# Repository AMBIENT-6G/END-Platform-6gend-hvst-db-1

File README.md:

# 6gend-hvst-db-1

Dual-Source Energy Harvesting Daughter Board for the END Platform

Part of the **AMBIENT-6G Energy Neutral Device (END) Platform**:
https://github.com/AMBIENT-6G/END-Platform

## Overview

The **6gend-hvst-db-1** is a dual-source energy harvesting daughter board for the END Platform based on the **e-peas AEM13921** energy harvesting PMIC. The board is intended as a research platform for investigating hybrid energy harvesting systems that combine **RF energy harvesting** with a second ambient energy source such as photovoltaic, thermal, vibration, or other DC energy harvesters.

The AEM13921 integrates two independent harvesting inputs, each featuring configurable Maximum Power Point Tracking (MPPT) or constant-voltage regulation. Harvested energy is stored in an external rechargeable storage element and supplied to the application through an integrated high-efficiency buck converter.

The board interfaces with an END Platform main board through the standard 12-pin END Platform connector and provides monitoring and configuration capabilities through an I²C interface.

## Features

- e-peas **AEM13921** dual-source energy harvesting PMIC
- Two independent energy harvesting inputs
- Simultaneous harvesting from both sources
- MPPT operation on both harvesting inputs
- Constant-voltage harvesting mode support
- Dedicated **5 V charging input**
- Integrated storage management
- Support for:
  - Supercapacitors
  - Lithium-Ion Capacitors (LiC)
  - Li-Ion batteries
  - LiPo batteries
- Integrated overcharge protection
- Integrated overdischarge protection
- Temperature monitoring of the storage element
- Configurable safety thresholds
- Average Power Monitoring (APM) through I²C
- Integrated high-efficiency buck converter
- Dynamic configuration through I²C
- Hardware configuration through solder-selectable GPIO settings
- Cold start from as low as **275 mV / 1.5 µW**
- Harvesting operation down to **120 mV after startup**
- END Platform compatible connector interface

## Board Image

[Picture of the PCB design in KiCAD](6gend-hvst-db-1.png)

## Purpose

The primary purpose of this board is to support research into:

- Hybrid energy harvesting systems
- RF energy harvesting
- Multi-source energy management
- Energy-neutral IoT systems
- Ambient energy harvesting optimization
- Storage technology evaluation
- Power-aware embedded systems
- Ultra-low-power wireless sensor nodes
- Energy availability monitoring and prediction

Typical applications combine an RF harvesting source with a second energy source such as:

- Solar cells
- Thermoelectric generators (TEGs)
- Piezoelectric harvesters
- Vibration harvesters
- Pulsed energy sources
- Other low-power DC sources

## Hardware Architecture

### AEM13921 Energy Harvesting PMIC

The board is built around the **e-peas AEM13921**, an ultra-efficient dual-source energy harvesting power management IC.

Key capabilities include:

- Two independent boost converters
- Independent MPPT configuration for each source
- Constant-voltage source regulation
- Simultaneous harvesting from both inputs
- Integrated storage charging and protection
- Integrated buck converter output
- Energy flow monitoring through Average Power Monitoring (APM)

The device can determine how much energy has been transferred from each harvesting source and from the 5 V charger into the storage element, as well as the energy delivered from storage to the load through its APM functionality.

### Energy Harvesting Inputs

The AEM13921 supports two harvesting channels.

Each input can be independently configured for:

- Open-circuit voltage ratio MPPT
- Constant-voltage regulation

This makes it possible to optimize energy extraction from a broad range of harvesting technologies while simultaneously harvesting from both sources.

A common use case is:

- Source 1: RF energy harvester
- Source 2: Solar cell

but other combinations are equally possible.

### 5 V Charging Input

In addition to the harvesting inputs, the board provides a dedicated **5 V charging input**.

This interface allows:

- Rapid charging of the storage element
- Recovery from depleted storage conditions
- Laboratory testing and characterization
- Development without requiring ambient energy sources

### Storage Management

The board supports a wide variety of rechargeable storage technologies including:

- Supercapacitors
- Lithium-Ion Capacitors (LiC)
- Lithium-Ion batteries
- Lithium-Polymer batteries

The AEM13921 provides configurable:

- Charge-ready thresholds
- Overcharge protection
- Overdischarge protection

These protection mechanisms increase storage lifetime and ensure safe operation.

### Thermal Monitoring

A dedicated temperature monitoring circuit is provided for the storage element.

This functionality allows:

- Monitoring storage temperature through the PMIC
- Over-temperature protection
- Under-temperature protection
- Safe charging and discharging operation

Temperature protection can be configured independently for charge and discharge conditions.

### Buck Converter Output

The harvested and stored energy is delivered to the application through the integrated high-efficiency buck converter.

Features include:

- Output voltage configurable between 0.6 V and 3.3 V
- High conversion efficiency
- Output current capability up to 100 mA

This allows efficient powering of ultra-low-power sensors, microcontrollers, and wireless communication systems.

### Configuration Interface

The board supports two configuration methods:

#### GPIO Configuration

The AEM13921 configuration pins can be statically configured using solder bridges on the PCB.

Depending on the solder bridge population, configuration pins may be tied:

- High
- Low

This allows standalone operation without software configuration.

#### I²C Configuration

All important system parameters can also be configured dynamically through I²C.

Available functionality includes:

- Reading system status
- Monitoring energy flow information
- Modifying PMIC operating parameters
- Reconfiguring protection thresholds
- Harvesting optimization

## Connector Pinout

The board follows the END Platform harvesting connector definition.

| Pin | Function |
|------|----------|
| 1 | NC |
| 2 | IRQ |
| 3 | SCL |
| 4 | SDA |
| 5 | GND |
| 6 | VCC |
| 7 | ST_LOAD |
| 8 | ST_STO |
| 9 | NC |
| 10 | NC |
| 11 | GND |
| 12 | VBAT |

## MCU Interface

Communication with the host controller is performed through **I²C**.

Required signals:

- SCL
- SDA
- IRQ

The host MCU can use the I²C interface to:

- Configure harvester settings
- Read energy monitoring information
- Read system status
- Monitor storage conditions
- Access thermal protection status

## Design Status

**Status: Under Debug**

The hardware has been:

- Designed
- Manufactured
- Assembled

Current activities:

- Hardware validation
- Firmware development
- Functional debugging
- System characterization

The board is operational but still undergoing verification and debugging.

## License

### CERN Open Hardware Licence Version 2 - Strongly Reciprocal (CERN-OHL-S-2.0)

This project is released under the **CERN Open Hardware Licence Version 2 - Strongly Reciprocal**.

You may:

- Study the design
- Modify the design
- Manufacture the design
- Distribute the design

provided that derivative hardware designs remain available under the same license.

A copy of the license can be obtained from:

https://cern-ohl.web.cern.ch/

## Citation

If you use this design in academic work, please cite:

6gend-hvst-db-1: Dual-Source Energy Harvesting Daughter Board for the END Platform,
DRAMCO Research Group, KU Leuven.

## Contact

**DRAMCO Research Group**  
KU Leuven – Ghent Campus  
Gebroeders De Smetstraat 1  
9000 Ghent  
Belgium

END Platform Repository:
https://github.com/AMBIENT-6G/END-Platform

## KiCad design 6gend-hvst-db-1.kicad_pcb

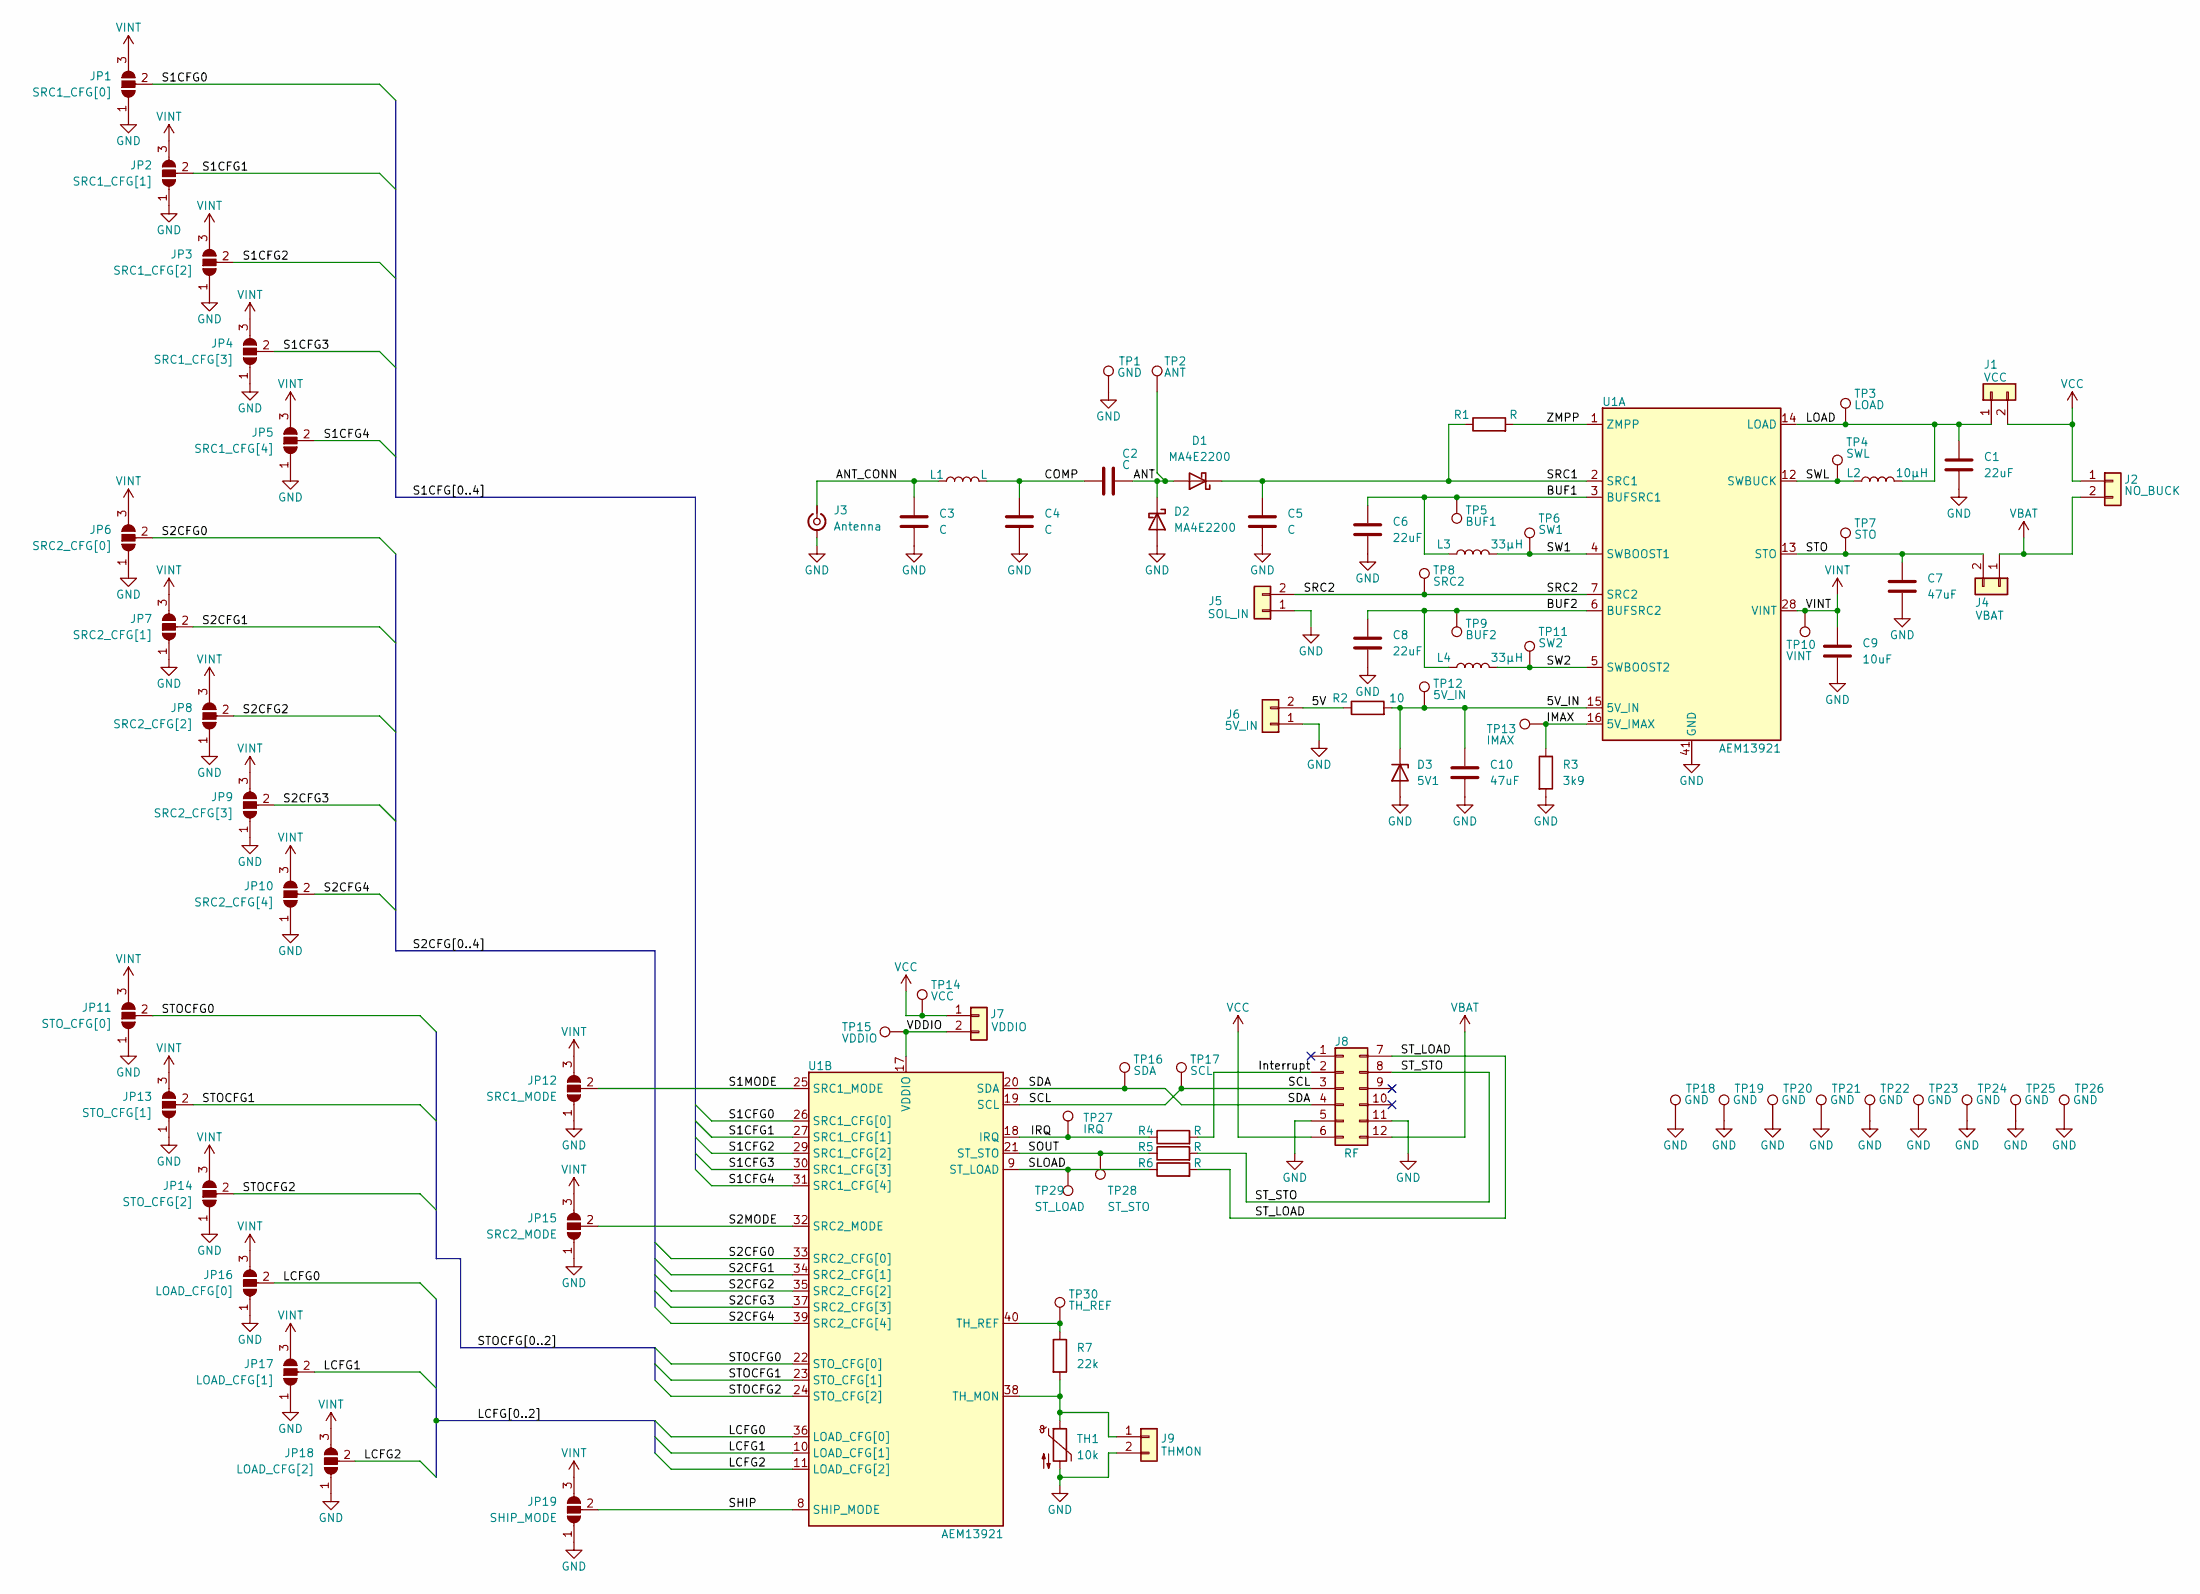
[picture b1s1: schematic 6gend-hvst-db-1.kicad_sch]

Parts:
C1, C6, C8: 22uF; C_0603_1608Metric; Part Number GRM188R61A226ME15D
C2, C3, C4, C5: C; C_0402_1005Metric
C7, C10: 47uF; C_0603_1608Metric; Part Number GRM188R60J476ME15D
C9: 10uF; C_0603_1608Metric
D1, D2: MA4E2200; D_SOD-323; Part Number MA4E2200A1-1141T
D3: 5V1; D_SOD-123; Part Number BZT52B5V1-E3-18
J1: VCC; PinHeader_1x02_P2.54mm_Vertical
J2: NO_BUCK; PinHeader_1x02_P2.54mm_Vertical
J3: Antenna; SMA_Amphenol_132134-16_Vertical; Part Number RFPC-SMA28-F
J4: VBAT; PinHeader_1x02_P2.54mm_Vertical
J5: SOL_IN; PhoenixContact_MC_1,5_2-G-3.81_1x02_P3.81mm_Horizontal; Part Number 1803277
J6: 5V_IN; PhoenixContact_MC_1,5_2-G-3.81_1x02_P3.81mm_Horizontal; Part Number 1803277
J7: VDDIO; PinHeader_1x02_P2.54mm_Vertical
J8: RF; PMOD_2x06_P2.54mm_Male; Part Number 61301221021
J9: THMON; PinHeader_1x02_P2.54mm_Vertical
JP1: SRC1_CFG[0]; SolderJumper-3_P2.0mm_Open_TrianglePad1.0x1.5mm
JP2: SRC1_CFG[1]; SolderJumper-3_P2.0mm_Open_TrianglePad1.0x1.5mm
JP3: SRC1_CFG[2]; SolderJumper-3_P2.0mm_Open_TrianglePad1.0x1.5mm
JP4: SRC1_CFG[3]; SolderJumper-3_P2.0mm_Open_TrianglePad1.0x1.5mm
JP5: SRC1_CFG[4]; SolderJumper-3_P2.0mm_Open_TrianglePad1.0x1.5mm
JP6: SRC2_CFG[0]; SolderJumper-3_P2.0mm_Open_TrianglePad1.0x1.5mm
JP7: SRC2_CFG[1]; SolderJumper-3_P2.0mm_Open_TrianglePad1.0x1.5mm
JP8: SRC2_CFG[2]; SolderJumper-3_P2.0mm_Open_TrianglePad1.0x1.5mm
JP9: SRC2_CFG[3]; SolderJumper-3_P2.0mm_Open_TrianglePad1.0x1.5mm
JP10: SRC2_CFG[4]; SolderJumper-3_P2.0mm_Open_TrianglePad1.0x1.5mm
JP11: STO_CFG[0]; SolderJumper-3_P2.0mm_Open_TrianglePad1.0x1.5mm
JP12: SRC1_MODE; SolderJumper-3_P2.0mm_Open_TrianglePad1.0x1.5mm
JP13: STO_CFG[1]; SolderJumper-3_P2.0mm_Open_TrianglePad1.0x1.5mm
JP14: STO_CFG[2]; SolderJumper-3_P2.0mm_Open_TrianglePad1.0x1.5mm
JP15: SRC2_MODE; SolderJumper-3_P2.0mm_Open_TrianglePad1.0x1.5mm
JP16: LOAD_CFG[0]; SolderJumper-3_P2.0mm_Open_TrianglePad1.0x1.5mm
JP17: LOAD_CFG[1]; SolderJumper-3_P2.0mm_Open_TrianglePad1.0x1.5mm
JP18: LOAD_CFG[2]; SolderJumper-3_P2.0mm_Open_TrianglePad1.0x1.5mm
JP19: SHIP_MODE; SolderJumper-3_P2.0mm_Open_TrianglePad1.0x1.5mm
L1: L; L_0402_1005Metric
L2: 10µH; L_1008_2520Metric; Part Number VLS252012CX-100M-1
L3, L4: 33µH; L_Coilcraft_LPS4018; Part Number VLS252012CX-100M-1
R1, R4, R5, R6: R; R_0603_1608Metric
R2: 10; R_0603_1608Metric
R3: 3k9; R_0603_1608Metric
R7: 22k; R_0603_1608Metric
TH1: 10k; R_0402_1005Metric; Part Number NCP15XH103J03RC
TP1: GND; Testpoint_SMD_S
TP2: ANT; Testpoint_SMD_S
TP3: LOAD; Testpoint_THT
TP4: SWL; Testpoint_THT
TP5: BUF1; Testpoint_THT
TP6: SW1; Testpoint_THT
TP7: STO; Testpoint_THT
TP8: SRC2; Testpoint_THT
TP9: BUF2; Testpoint_THT
TP10: VINT; Testpoint_THT
TP11: SW2; Testpoint_THT
TP12: 5V_IN; Testpoint_THT
TP13: IMAX; Testpoint_THT
TP14: VCC; Testpoint_THT
TP15: VDDIO; Testpoint_THT
TP16: SDA; Testpoint_THT
TP17: SCL; Testpoint_THT
TP18, TP19, TP20, TP21, TP22, TP23, TP24, TP25, TP26: GND; Testpoint_THT_Marked
TP27: IRQ; Testpoint_THT
TP28: ST_STO; Testpoint_THT
TP29: ST_LOAD; Testpoint_THT
TP30: TH_REF; Testpoint_THT
U1: AEM13921; QFN-40-1EP_5x5mm_P0.4mm_EP3.6x3.6mm

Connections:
/5V: J6.2, R2.1
/5V_IN: C10.1, D3.1 (K), R2.2, TP12.1 (1_1), U1.15 (5V_IN)
/ANT: C2.2, D1.2 (A), D2.1 (K), TP2.1 (1_1)
/ANT_CONN: C3.1, J3.1 (In), L1.1
/BUF1: C6.1, L3.1, TP5.1 (1_1), U1.3 (BUFSRC1)
/BUF2: C8.1, L4.1, TP9.1 (1_1), U1.6 (BUFSRC2)
/COMP: C2.1, C4.1, L1.2
/IMAX: R3.1, TP13.1 (1_1), U1.16 (5V_IMAX)
/IRQ: R4.1, TP27.1 (1_1), U1.18 (IRQ)
/Interrupt: J8.2, R4.2
/LCFG0: JP16.2 (C), U1.36 (LOAD_CFG[0])
/LCFG1: JP17.2 (C), U1.10 (LOAD_CFG[1])
/LCFG2: JP18.2 (C), U1.11 (LOAD_CFG[2])
/LOAD: C1.1, J1.1, L2.2, TP3.1 (1_1), U1.14 (LOAD)
/S1CFG0: JP1.2 (C), U1.26 (SRC1_CFG[0])
/S1CFG1: JP2.2 (C), U1.27 (SRC1_CFG[1])
/S1CFG2: JP3.2 (C), U1.29 (SRC1_CFG[2])
/S1CFG3: JP4.2 (C), U1.30 (SRC1_CFG[3])
/S1CFG4: JP5.2 (C), U1.31 (SRC1_CFG[4])
/S1MODE: JP12.2 (C), U1.25 (SRC1_MODE)
/S2CFG0: JP6.2 (C), U1.33 (SRC2_CFG[0])
/S2CFG1: JP7.2 (C), U1.34 (SRC2_CFG[1])
/S2CFG2: JP8.2 (C), U1.35 (SRC2_CFG[2])
/S2CFG3: JP9.2 (C), U1.37 (SRC2_CFG[3])
/S2CFG4: JP10.2 (C), U1.39 (SRC2_CFG[4])
/S2MODE: JP15.2 (C), U1.32 (SRC2_MODE)
/SCL: J8.3, TP17.1 (1_1), U1.19 (SCL)
/SDA: J8.4, TP16.1 (1_1), U1.20 (SDA)
/SHIP: JP19.2 (C), U1.8 (SHIP_MODE)
/SLOAD: R6.1, TP29.1 (1_1), U1.9 (ST_LOAD)
/SOUT: R5.1, TP28.1 (1_1), U1.21 (ST_STO)
/SRC1: C5.1, D1.1 (K), R1.1, U1.2 (SRC1)
/SRC2: J5.2, TP8.1 (1_1), U1.7 (SRC2)
/STO: C7.1, J4.2, TP7.1 (1_1), U1.13 (STO)
/STOCFG0: JP11.2 (C), U1.22 (STO_CFG[0])
/STOCFG1: JP13.2 (C), U1.23 (STO_CFG[1])
/STOCFG2: JP14.2 (C), U1.24 (STO_CFG[2])
/ST_LOAD: J8.7, R6.2
/ST_STO: J8.8, R5.2
/SW1: L3.2, TP6.1 (1_1), U1.4 (SWBOOST1)
/SW2: L4.2, TP11.1 (1_1), U1.5 (SWBOOST2)
/SWL: L2.1, TP4.1 (1_1), U1.12 (SWBUCK)
/VDDIO: J7.2, TP15.1 (1_1), U1.17 (VDDIO)
/ZMPP: R1.2, U1.1 (ZMPP)
GND: C1.2, C3.2, C4.2, C5.2, C6.2, C7.2, C8.2, C9.2, C10.2, D2.2 (A), D3.2 (A), J3.2 (Ext), J5.1, J6.1, J8.5, J8.11, J9.2, JP1.1 (A), JP2.1 (A), JP3.1 (A), JP4.1 (A), JP5.1 (A), JP6.1 (A), JP7.1 (A), JP8.1 (A), JP9.1 (A), JP10.1 (A), JP11.1 (A), JP12.1 (A), JP13.1 (A), JP14.1 (A), JP15.1 (A), JP16.1 (A), JP17.1 (A), JP18.1 (A), JP19.1 (A), R3.2, TH1.2, TP1.1 (1_1), TP18.1 (1_1), TP19.1 (1_1), TP20.1 (1_1), TP21.1 (1_1), TP22.1 (1_1), TP23.1 (1_1), TP24.1 (1_1), TP25.1 (1_1), TP26.1 (1_1), U1.41 (GND)
unnamed: J9.1, R7.2, TH1.1, U1.38 (TH_MON)
unnamed: R7.1, TP30.1 (1_1), U1.40 (TH_REF)
VBAT: J2.2, J4.1, J8.12
VCC: J1.2, J2.1, J7.1, J8.6, TP14.1 (1_1)
VINT: C9.1, JP1.3 (B), JP2.3 (B), JP3.3 (B), JP4.3 (B), JP5.3 (B), JP6.3 (B), JP7.3 (B), JP8.3 (B), JP9.3 (B), JP10.3 (B), JP11.3 (B), JP12.3 (B), JP13.3 (B), JP14.3 (B), JP15.3 (B), JP16.3 (B), JP17.3 (B), JP18.3 (B), JP19.3 (B), TP10.1 (1_1), U1.28 (VINT)

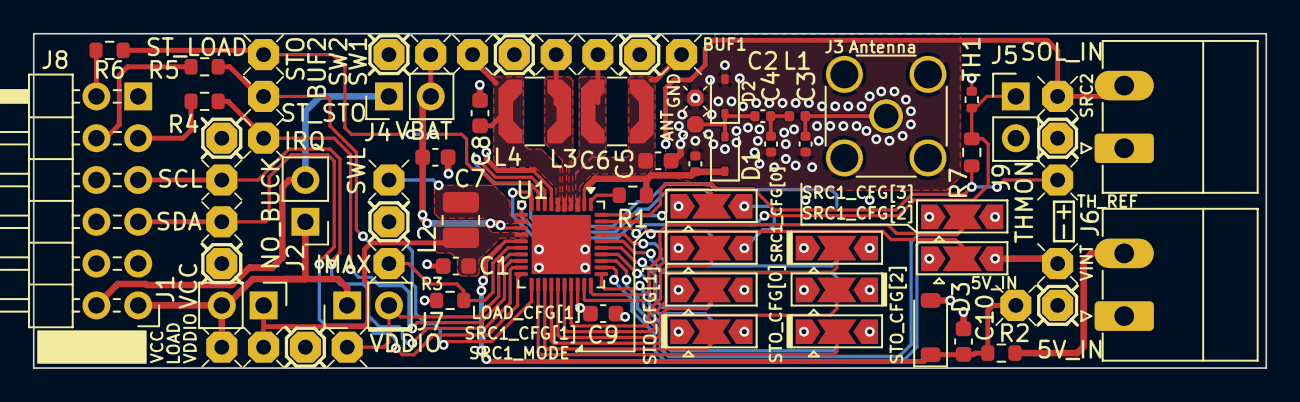
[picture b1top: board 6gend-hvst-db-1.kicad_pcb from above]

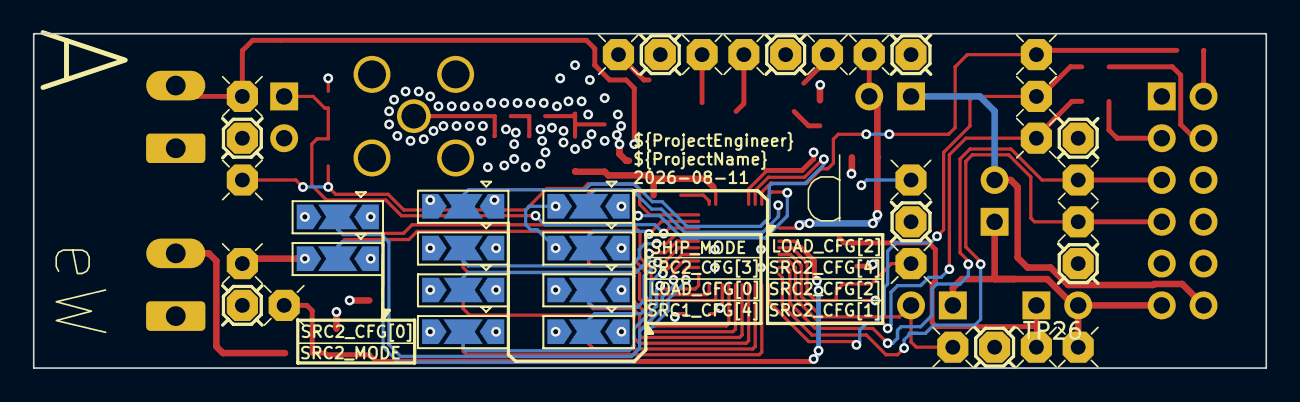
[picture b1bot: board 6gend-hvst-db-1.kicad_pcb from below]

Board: 4 copper layers, 74.9 x 20.3 mm, 84 parts (10 on the bottom side), 50 nets.
